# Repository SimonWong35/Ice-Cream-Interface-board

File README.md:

# Ice-Cream-Interface-board
This interface board is to test out the functionality of the Arduino codes of the students.

## Schematic

## Layout

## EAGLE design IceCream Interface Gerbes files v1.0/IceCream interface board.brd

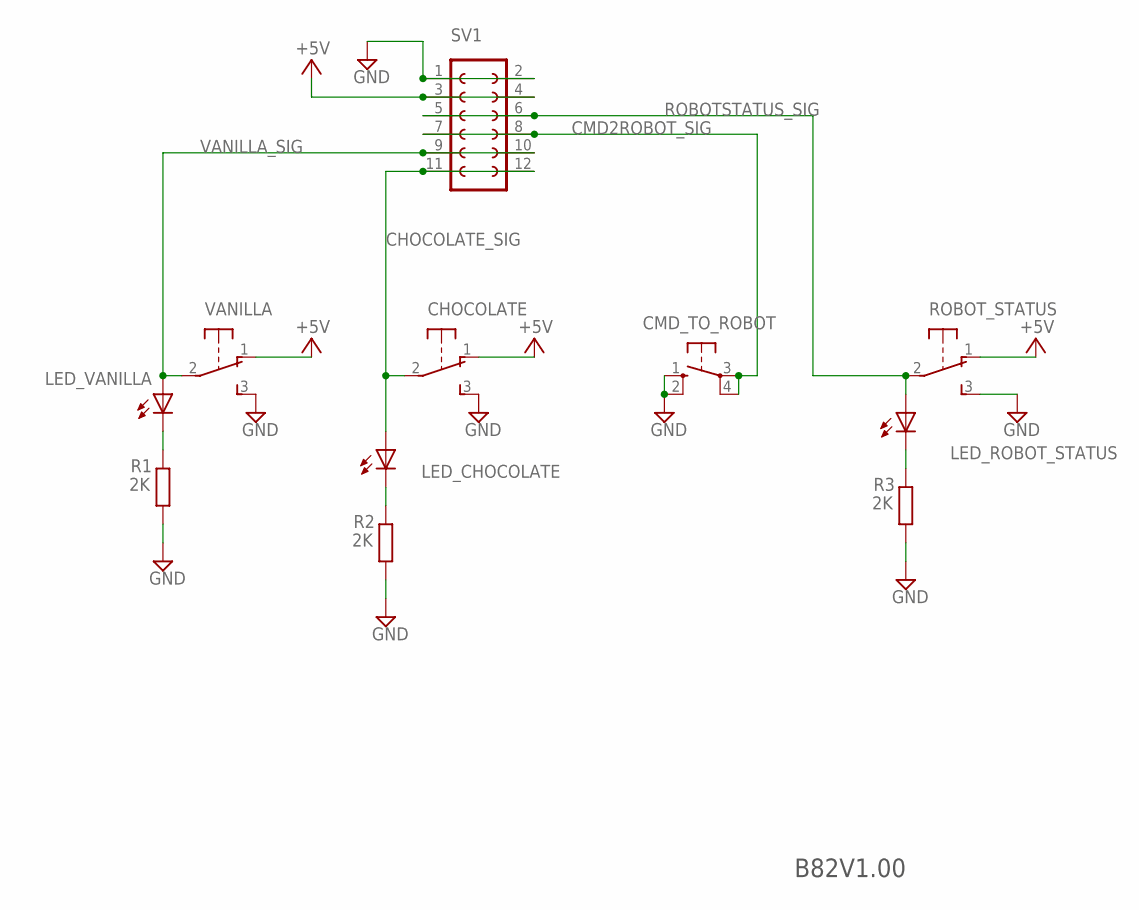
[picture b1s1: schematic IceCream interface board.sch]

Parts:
CHOCOLATE: TOGGLE_SW; MA03-1
CMD_TO_ROBOT: TACT_SWITCH; B3F-10XX
LED_CHOCOLATE: LED5MM
LED_ROBOT_STATUS: LED5MM
LED_VANILLA: LED5MM
R1, R2, R3: 2K; 0207/10
ROBOT_STATUS: TOGGLE_SW; MA03-1
SV1: FE06-2
VANILLA: TOGGLE_SW; MA03-1

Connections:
+5V: CHOCOLATE.1 (O), ROBOT_STATUS.1 (O), SV1.3, SV1.4, VANILLA.1 (O)
CHOCOLATE_SIG: CHOCOLATE.2, LED_CHOCOLATE.A, SV1.11, SV1.12
CMD2ROBOT_SIG: CMD_TO_ROBOT.3, CMD_TO_ROBOT.4 (P1), SV1.7, SV1.8
GND: CHOCOLATE.3 (S), CMD_TO_ROBOT.1 (S), CMD_TO_ROBOT.2 (S1), R1.1, R2.1, R3.1, ROBOT_STATUS.3 (S), SV1.1, SV1.2, VANILLA.3 (S)
unnamed: LED_VANILLA.K (C), R1.2
unnamed: LED_CHOCOLATE.K (C), R2.2
unnamed: LED_ROBOT_STATUS.K (C), R3.2
ROBOTSTATUS_SIG: LED_ROBOT_STATUS.A, ROBOT_STATUS.2, SV1.5, SV1.6
VANILLA_SIG: LED_VANILLA.A, SV1.9, SV1.10, VANILLA.2

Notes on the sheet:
B82V1.00

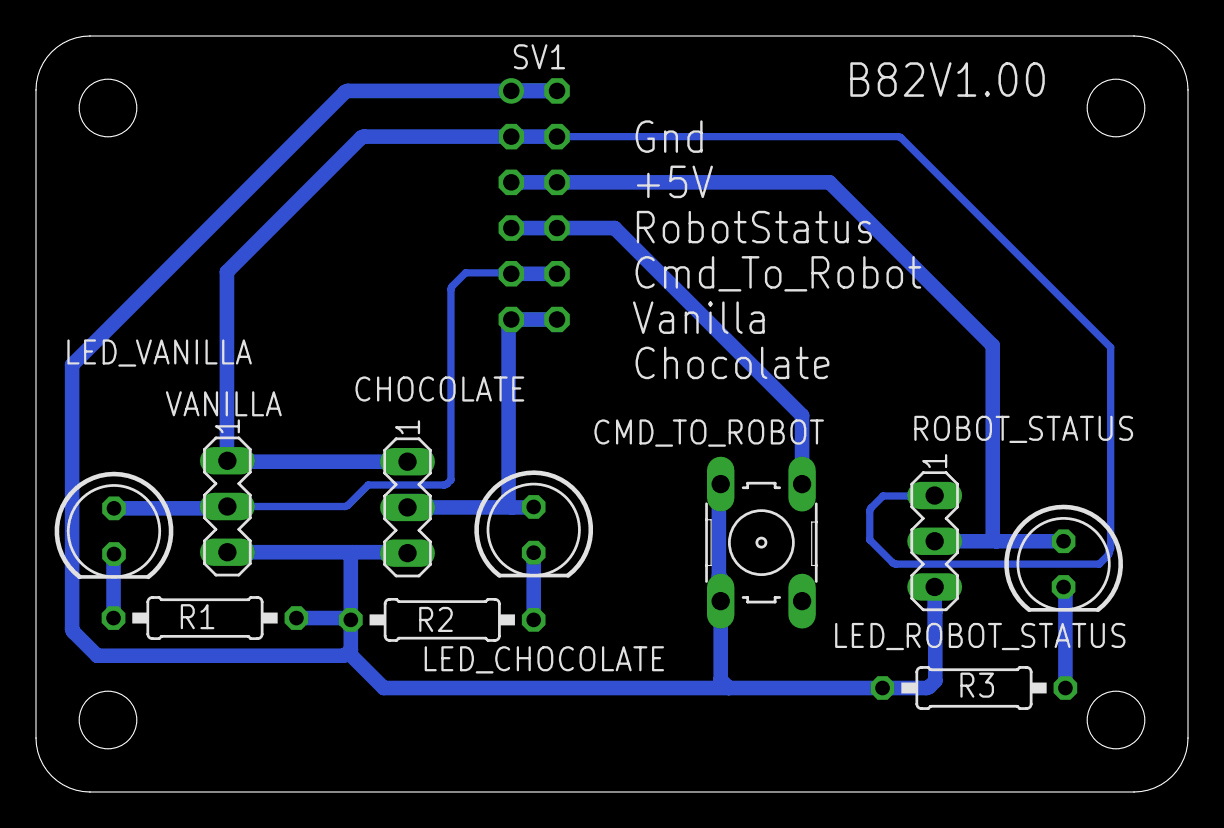
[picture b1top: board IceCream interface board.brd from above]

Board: 2 copper layers, 64.0 x 42.0 mm, 11 parts (1 on the bottom side), 9 nets.
